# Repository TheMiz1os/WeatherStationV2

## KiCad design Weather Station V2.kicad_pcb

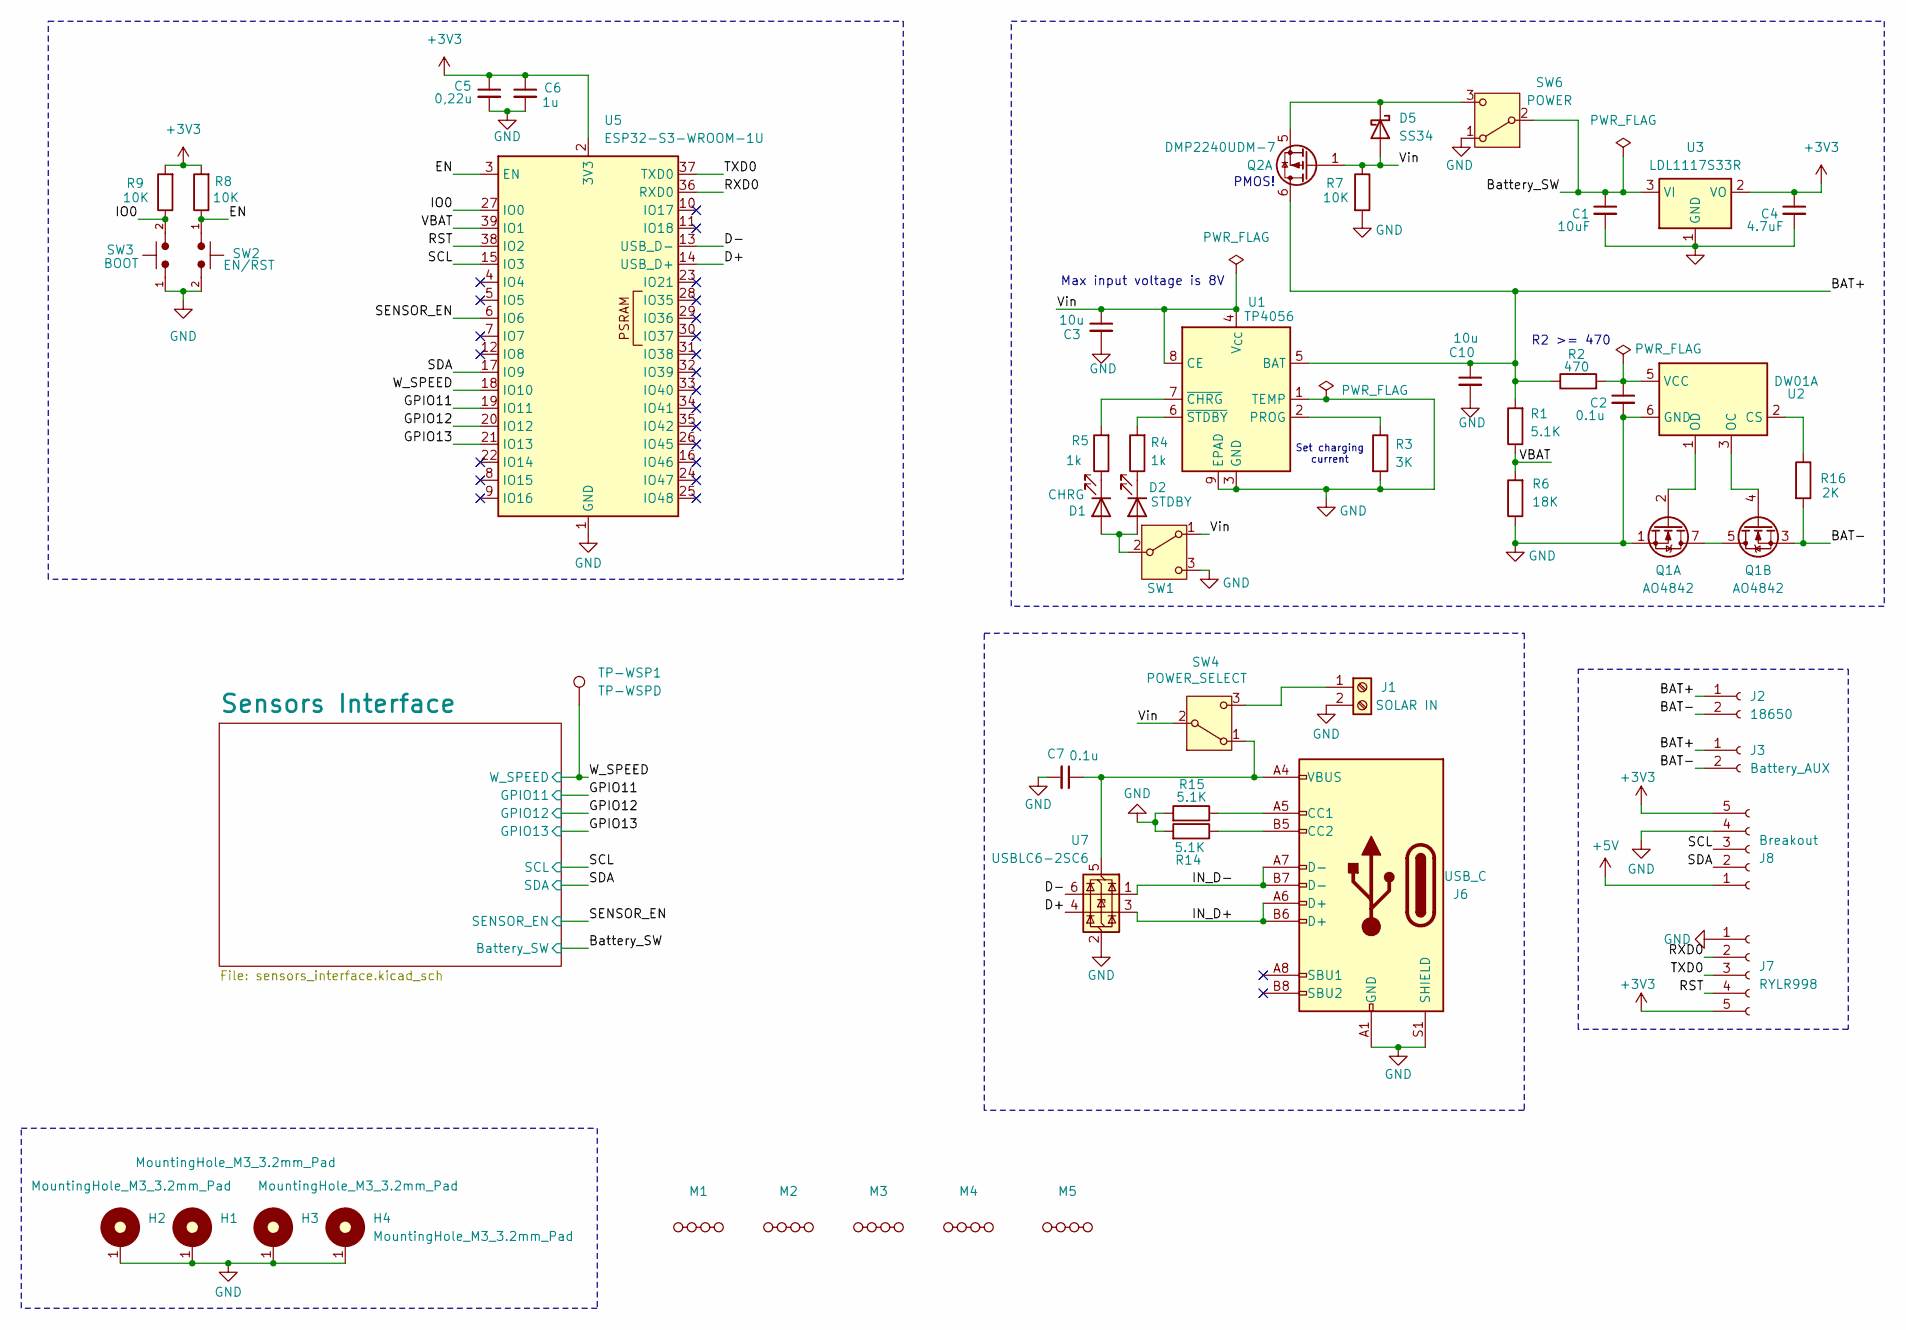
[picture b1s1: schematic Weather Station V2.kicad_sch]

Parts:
C1: 10uF; C_1206_3216Metric
C2, C7: 0.1u; C_1206_3216Metric
C3, C10: 10u; C_1206_3216Metric
C4: 4.7uF; C_1206_3216Metric
C5: 0,22u; C_1206_3216Metric
C6: 1u; C_1206_3216Metric
D1: CHRG; LED_1206_3216Metric
D2: STDBY; LED_1206_3216Metric
D5: SS34; D_SMA
H1, H2, H3, H4: MountingHole_M3_3.2mm_Pad; MountingHole_3.2mm_Pad
J1: SOLAR IN; TerminalBlock_MaiXu_MX126-5.0-02P_1x02_P5.00mm
J2: 18650; BatteryHolder_MPD_BH-18650-PC
J3: Battery_AUX; JST_EH_B2B-EH-A_1x02_P2.50mm_Vertical
J6: USB_C; USB_C_Receptacle_GCT_USB4105-xx-A_16P_TopMnt_Horizontal
J7: RYLR998; PinSocket_1x05_P2.54mm_Vertical
J8: Breakout; PinSocket_1x05_P2.54mm_Vertical
M1, M2, M3, M4, M5: MouseBites, Cosmetic, JLCPCB, 1.6mm
Q1: AO4842; SOIC-8_3.9x4.9mm_P1.27mm
Q2: DMP2240UDM-7; SOT-23-6_Handsoldering
R1, R14, R15: 5.1K; R_1206_3216Metric
R2: 470; R_1206_3216Metric
R3: 3K; R_1206_3216Metric
R4, R5: 1k; R_1206_3216Metric
R6: 18K; R_1206_3216Metric
R7, R8, R9: 10K; R_1206_3216Metric
R16: 2K; R_1206_3216Metric
SW1: LED_ENABLE; Slide_Switch_SPDT_P3mm_10x5x10mm
SW2: EN/RST; SW_PUSH_6mm
SW3: BOOT; SW_PUSH_6mm
SW4: POWER_SELECT; Slide_Switch_SPDT_P3mm_10x5x10mm
SW6: POWER; Slide_Switch_SPDT_P3mm_10x5x10mm
TP-WSP1: TP-WSPD; TestPoint_THTPad_D2.0mm_Drill1.0mm
U1: TP4056; SOIC-8-1EP_3.9x4.9mm_P1.27mm_EP2.41x3.3mm_ThermalVias
U2: DW01A; SOT-23-6_Handsoldering
U3: LDL1117S33R; SOT-223-3_TabPin2
U5: ESP32-S3-WROOM-1U
U7: USBLC6-2SC6; SOT-23-6

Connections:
+3V3: C4.1, C5.1, C6.1, J7.5, J8.5, R8.2, R9.2, U3.2 (VO), U5.2 (3V3); also elsewhere on the board
+5V: J8.1; also elsewhere on the board
/BAT+: C10.1, J2.1, J3.1, Q2.6 (D), R1.2, R2.1, U1.5 (BAT)
/BAT-: J2.2, J3.2, Q1.3 (S2), R16.2
/Battery_SW: C1.1, SW6.2 (B), U3.3 (VI); also elsewhere on the board
/D+: U5.14 (USB_D+), U7.4 (I/O2)
/D-: U5.13 (USB_D-), U7.6 (I/O1)
/EN: R8.1, SW2.1, U5.3 (EN)
/GPIO11: U5.19 (IO11); also elsewhere on the board
/GPIO12: U5.20 (IO12); also elsewhere on the board
/GPIO13: U5.21 (IO13); also elsewhere on the board
/IN_D+: J6.A6 (D+), J6.B6 (D+), U7.3 (I/O2)
/IN_D-: J6.A7 (D-), J6.B7 (D-), U7.1 (I/O1)
/IO0: R9.1, SW3.2, U5.27 (IO0)
/RST: J7.4, U5.38 (IO2)
/RXD0: J7.2, U5.36 (RXD0)
/SCL: J8.3, U5.15 (IO3); also elsewhere on the board
/SDA: J8.2, U5.17 (IO9); also elsewhere on the board
/SENSOR_EN: U5.6 (IO6); also elsewhere on the board
/TXD0: J7.3, U5.37 (TXD0)
/VBAT: R1.1, R6.2, U5.39 (IO1)
/Vin: C3.1, D5.2 (A), Q2.1 (G), R7.1, SW1.1 (A), SW4.2 (B), U1.4 (V_{CC}), U1.8 (CE)
/W_SPEED: TP-WSP1.1, U5.18 (IO10); also elsewhere on the board
GND: C1.2, C2.2, C3.2, C4.2, C5.2, C6.2, C7.2, C10.2, H1.1, H2.1, H3.1, H4.1, J1.2, J6.A1 (GND), J6.A12 (GND), J6.B1 (GND), J6.B12 (GND), J6.S1 (SHIELD), J7.1, J8.4, Q1.1 (S1), R3.2, R6.1, R7.2, R14.2, R15.2, SW1.3 (C), SW2.2, SW3.1, SW6.1 (A), U1.1 (TEMP), U1.3 (GND), U1.9 (EPAD), U2.6 (GND), U3.1 (GND), U5.1 (GND), U5.40 (GND), U5.41 (GND), U7.2 (GND); also elsewhere on the board
unnamed: D1.2 (A), D2.2 (A), SW1.2 (B)
unnamed: D1.1 (K), R5.1
unnamed: D2.1 (K), R4.1
unnamed: D5.1 (K), Q2.5 (S), SW6.3 (C)
unnamed: J1.1, SW4.3 (C)
unnamed: J6.A5 (CC1), R15.1
unnamed: J6.B5 (CC2), R14.1
unnamed: Q1.5 (D2), Q1.6 (D2), Q1.7 (D1), Q1.8 (D1)
unnamed: Q1.2 (G1), U2.1 (OD)
unnamed: Q1.4 (G2), U2.3 (OC)
unnamed: C7.1, J6.A4 (VBUS), J6.A9 (VBUS), J6.B4 (VBUS), J6.B9 (VBUS), SW4.1 (A), U7.5 (VBUS)
unnamed: R3.1, U1.2 (PROG)
unnamed: R5.2, U1.7 (~CHRG)
unnamed: R4.2, U1.6 (~STDBY)
unnamed: R16.1, U2.2 (CS)
unnamed: C2.1, R2.2, U2.5 (VCC)

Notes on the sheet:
R2 >= 470
PMOS!
Set charging current
Max input voltage is 8V

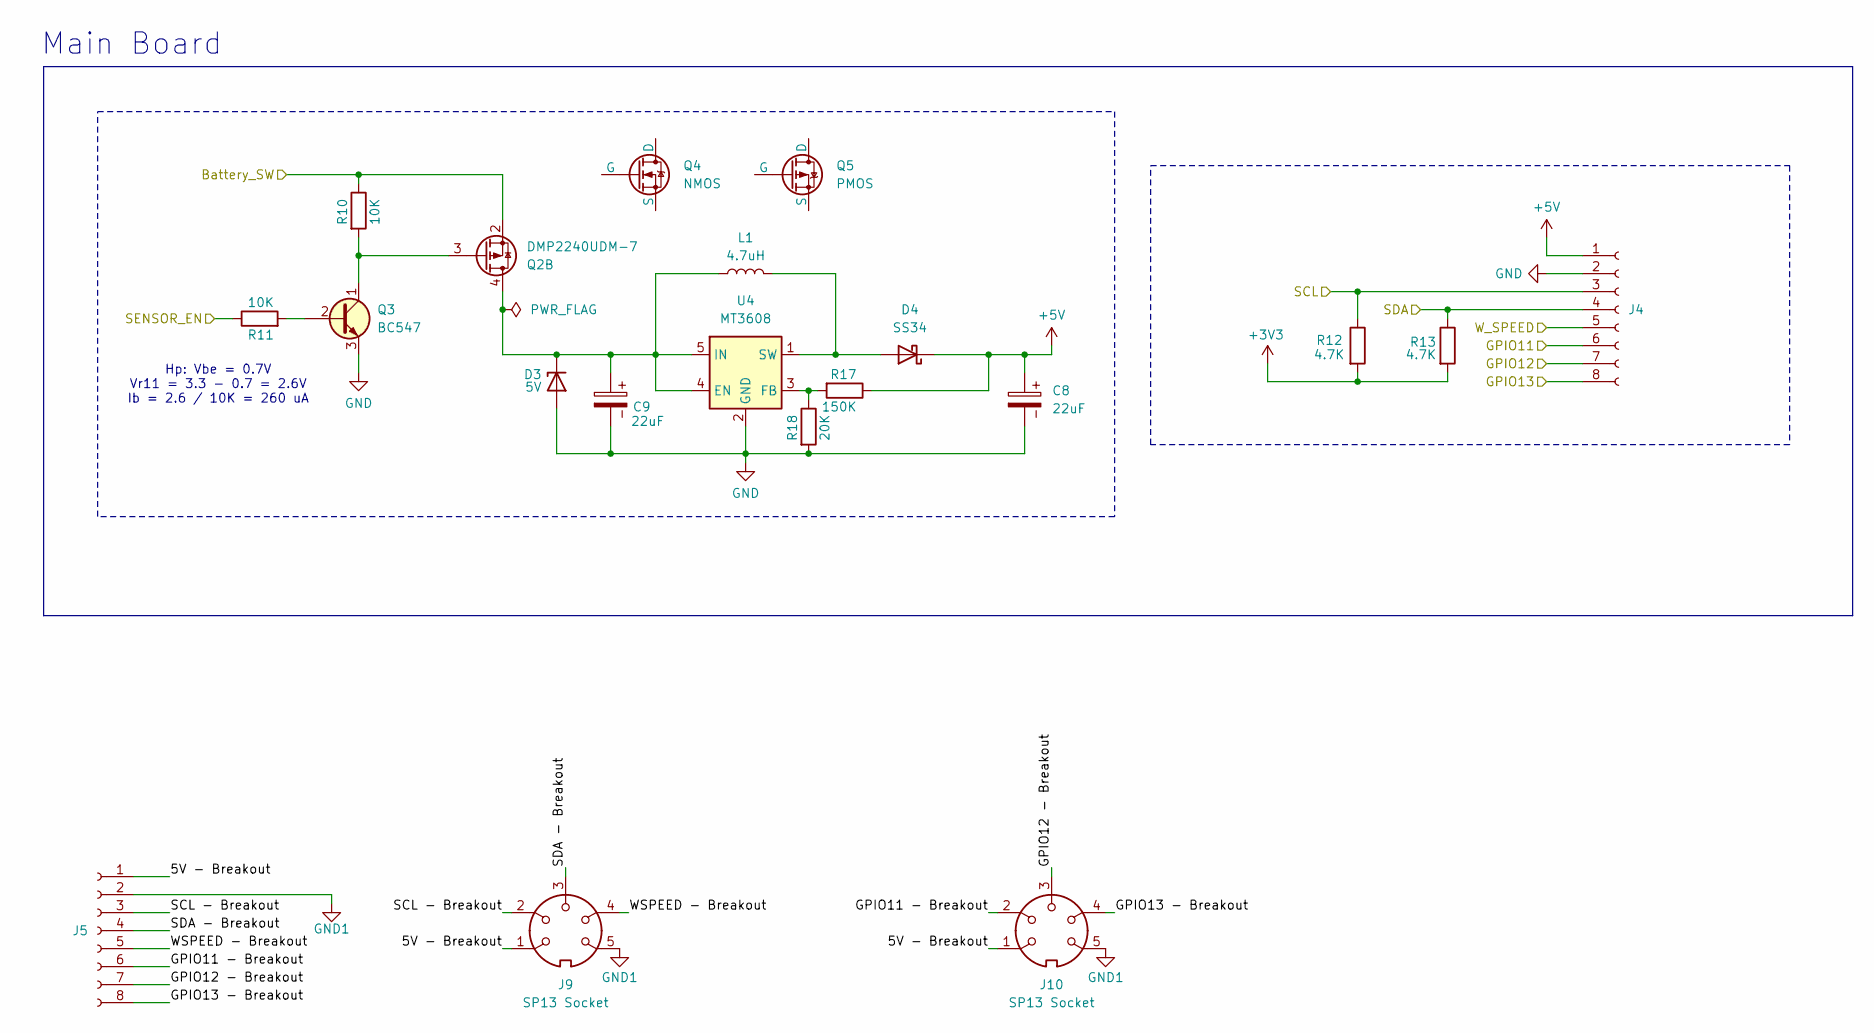
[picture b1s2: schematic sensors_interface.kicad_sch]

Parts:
C8, C9: 22uF; CP_Radial_D4.0mm_P1.50mm
D3: 5V; D_DO-41_SOD81_P10.16mm_Horizontal
D4: SS34; D_SMA
J4, J5: Conn_01x08_Socket; Hirose_DF13-08P-1.25DSA_1x08_P1.25mm_Vertical
J9, J10: SP13 Socket; SP13_5pin_holes
L1: 4.7uH; L_APV_APH0420
Q2: DMP2240UDM-7; SOT-23-6_Handsoldering
Q3: BC547; TO-92_Inline_Wide_CBE
Q4: NMOS
Q5: PMOS
R10, R11: 10K; R_1206_3216Metric
R12, R13: 4.7K; R_1206_3216Metric
R17: 150K; R_1206_3216Metric
R18: 20K; R_1206_3216Metric
U4: MT3608; SOT-23-6

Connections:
+3V3: R12.2, R13.2; also elsewhere on the board
+5V: C8.1, D4.1 (K), J4.1, R17.1; also elsewhere on the board
/Battery_SW: Q2.2 (S), R10.1; also elsewhere on the board
/GPIO11: J4.6; also elsewhere on the board
/GPIO12: J4.7; also elsewhere on the board
/GPIO13: J4.8; also elsewhere on the board
/SCL: J4.3, R12.1; also elsewhere on the board
/SDA: J4.4, R13.1; also elsewhere on the board
/SENSOR_EN: R11.1; also elsewhere on the board
/Sensors Interface/5V - Breakout: J5.1, J9.1, J10.1
/Sensors Interface/GPIO11 - Breakout: J5.6, J10.2
/Sensors Interface/GPIO12 - Breakout: J5.7, J10.3
/Sensors Interface/GPIO13 - Breakout: J5.8, J10.4
/Sensors Interface/SCL - Breakout: J5.3, J9.2
/Sensors Interface/SDA - Breakout: J5.4, J9.3
/Sensors Interface/WSPEED - Breakout: J5.5, J9.4
/W_SPEED: J4.5; also elsewhere on the board
GND: C8.2, C9.2, D3.2 (A), J4.2, Q3.3 (E), R18.2, U4.2 (GND); also elsewhere on the board
GND1: J5.2, J9.5, J10.5
unnamed: C9.1, D3.1 (K), L1.1, Q2.4 (D), U4.4 (EN), U4.5 (IN)
unnamed: D4.2 (A), L1.2, U4.1 (SW)
unnamed: Q2.3 (G), Q3.1 (C), R10.2
unnamed: Q3.2 (B), R11.2
unnamed: R17.2, R18.1, U4.3 (FB)

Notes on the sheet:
Main Board
Hp: Vbe = 0.7V Vr11 = 3.3 - 0.7 = 2.6V Ib = 2.6 / 10K = 260 uA

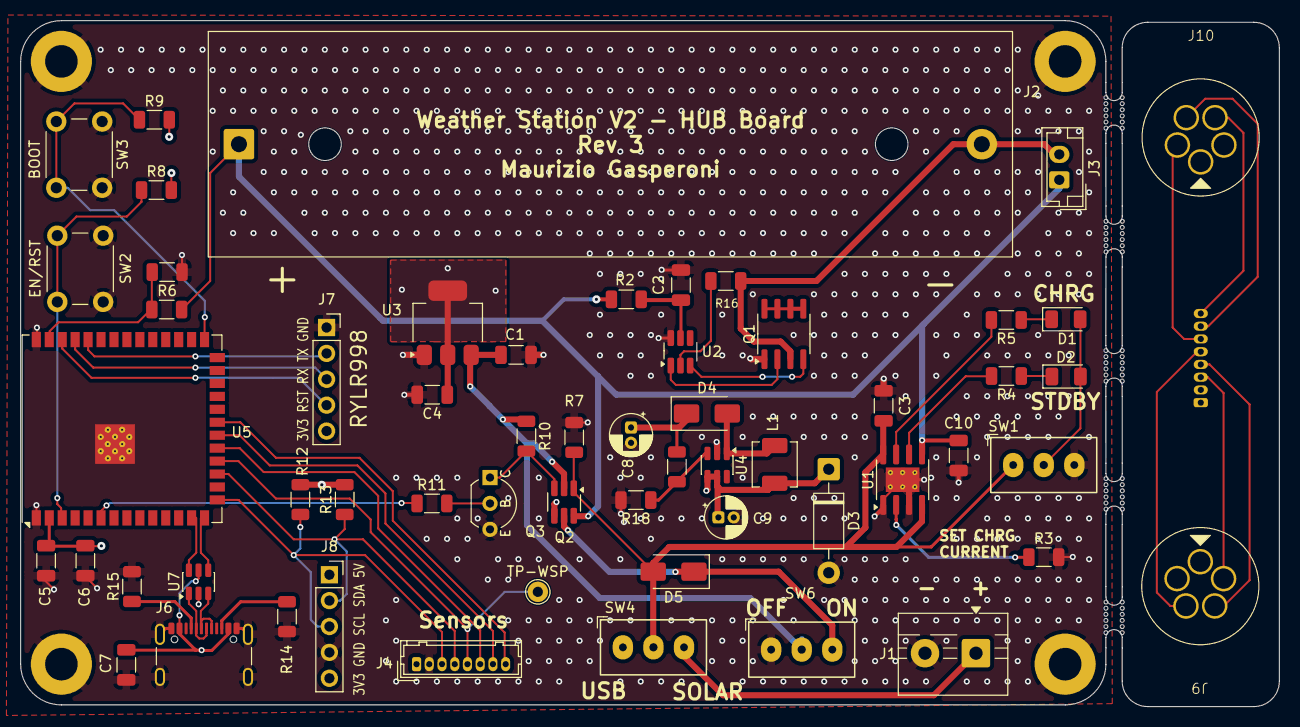
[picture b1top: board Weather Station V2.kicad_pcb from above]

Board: 4 copper layers, 123.5 x 67.3 mm, 68 parts (1 on the bottom side), 53 nets.

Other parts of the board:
TP-WSP: TP-WSPD; TestPoint_THTPad_D2.0mm_Drill1.0mm

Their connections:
/W_SPEED: TP-WSP.1 (1_1); also elsewhere on the board

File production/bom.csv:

Designator,Footprint,Quantity,Value,LCSC Part #
C1,1206,1,10uF,
"C2, C3, C7",1206,3,0.1u,
C4,1206,1,4.7uF,
C5,1206,1,"0,22u",
C6,1206,1,1u,
"C8, C9",CP_Radial_D4.0mm_P1.50mm,2,22uF,
D1,1206,1,CHRG,
D2,1206,1,STDBY,
D3,D_DO-41_SOD81_P10.16mm_Horizontal,1,5V,
"D4, D5",D_SMA,2,SS34,
"H1, H2, H3, H4",MountingHole_3.2mm_Pad,4,MountingHole_M3_3.2mm_Pad,
J1,TerminalBlock_MaiXu_MX126-5.0-02P_1x02_P5.00mm,1,SOLAR IN,
J2,BatteryHolder_MPD_BH-18650-PC,1,18650,
J3,JST_EH_B2B-EH-A_1x02_P2.50mm_Vertical,1,Battery_AUX,
J4,Hirose_DF13-08P-1.25DSA_1x08_P1.25mm_Vertical,1,Conn_01x08_Socket,
J6,USB_C_Receptacle_GCT_USB4105-xx-A_16P_TopMnt_Horizontal,1,USB_C,
J7,PinSocket_1x05_P2.54mm_Vertical,1,RYLR998,
J8,PinSocket_1x05_P2.54mm_Vertical,1,Breakout,
L1,L_APV_APH0420,1,4.7uH,
Q1,SOIC-8_3.9x4.9mm_P1.27mm,1,AO4842,
Q2,SOT-23-6_Handsoldering,1,DMP2240UDM-7,
Q3,TO-92_Inline_Wide_CBE,1,BC547,
"R1, R14, R15",1206,3,5.1K,
"R10, R11, R7, R8, R9",1206,5,10K,
"R12, R13",1206,2,4.7K,
R16,1206,1,5K,
R17,1206,1,150K,
R18,1206,1,20K,
R2,1206,1,100,
R3,1206,1,3K,
"R4, R5",1206,2,330,
R6,1206,1,18K,
SW1,Slide_Switch_SPDT_P3mm_10x5x10mm,1,LED_ENABLE,
SW2,SW_PUSH_6mm,1,EN/RST,
SW3,SW_PUSH_6mm,1,BOOT,
SW4,Slide_Switch_SPDT_P3mm_10x5x10mm,1,POWER_SELECT,
SW6,Slide_Switch_SPDT_P3mm_10x5x10mm,1,POWER,
U1,SOIC-8-1EP_3.9x4.9mm_P1.27mm_EP2.41x3.3mm_ThermalVias,1,TP4056,
U2,SOT-23-6_Handsoldering,1,DW01A,
U3,SOT-223-3_TabPin2,1,LDL1117S33R,
U4,SOT-23-6,1,MT3608,
U5,ESP32-S3-WROOM-1U,1,ESP32-S3-WROOM-1U,
U7,SOT-23-6,1,USBLC6-2SC6,

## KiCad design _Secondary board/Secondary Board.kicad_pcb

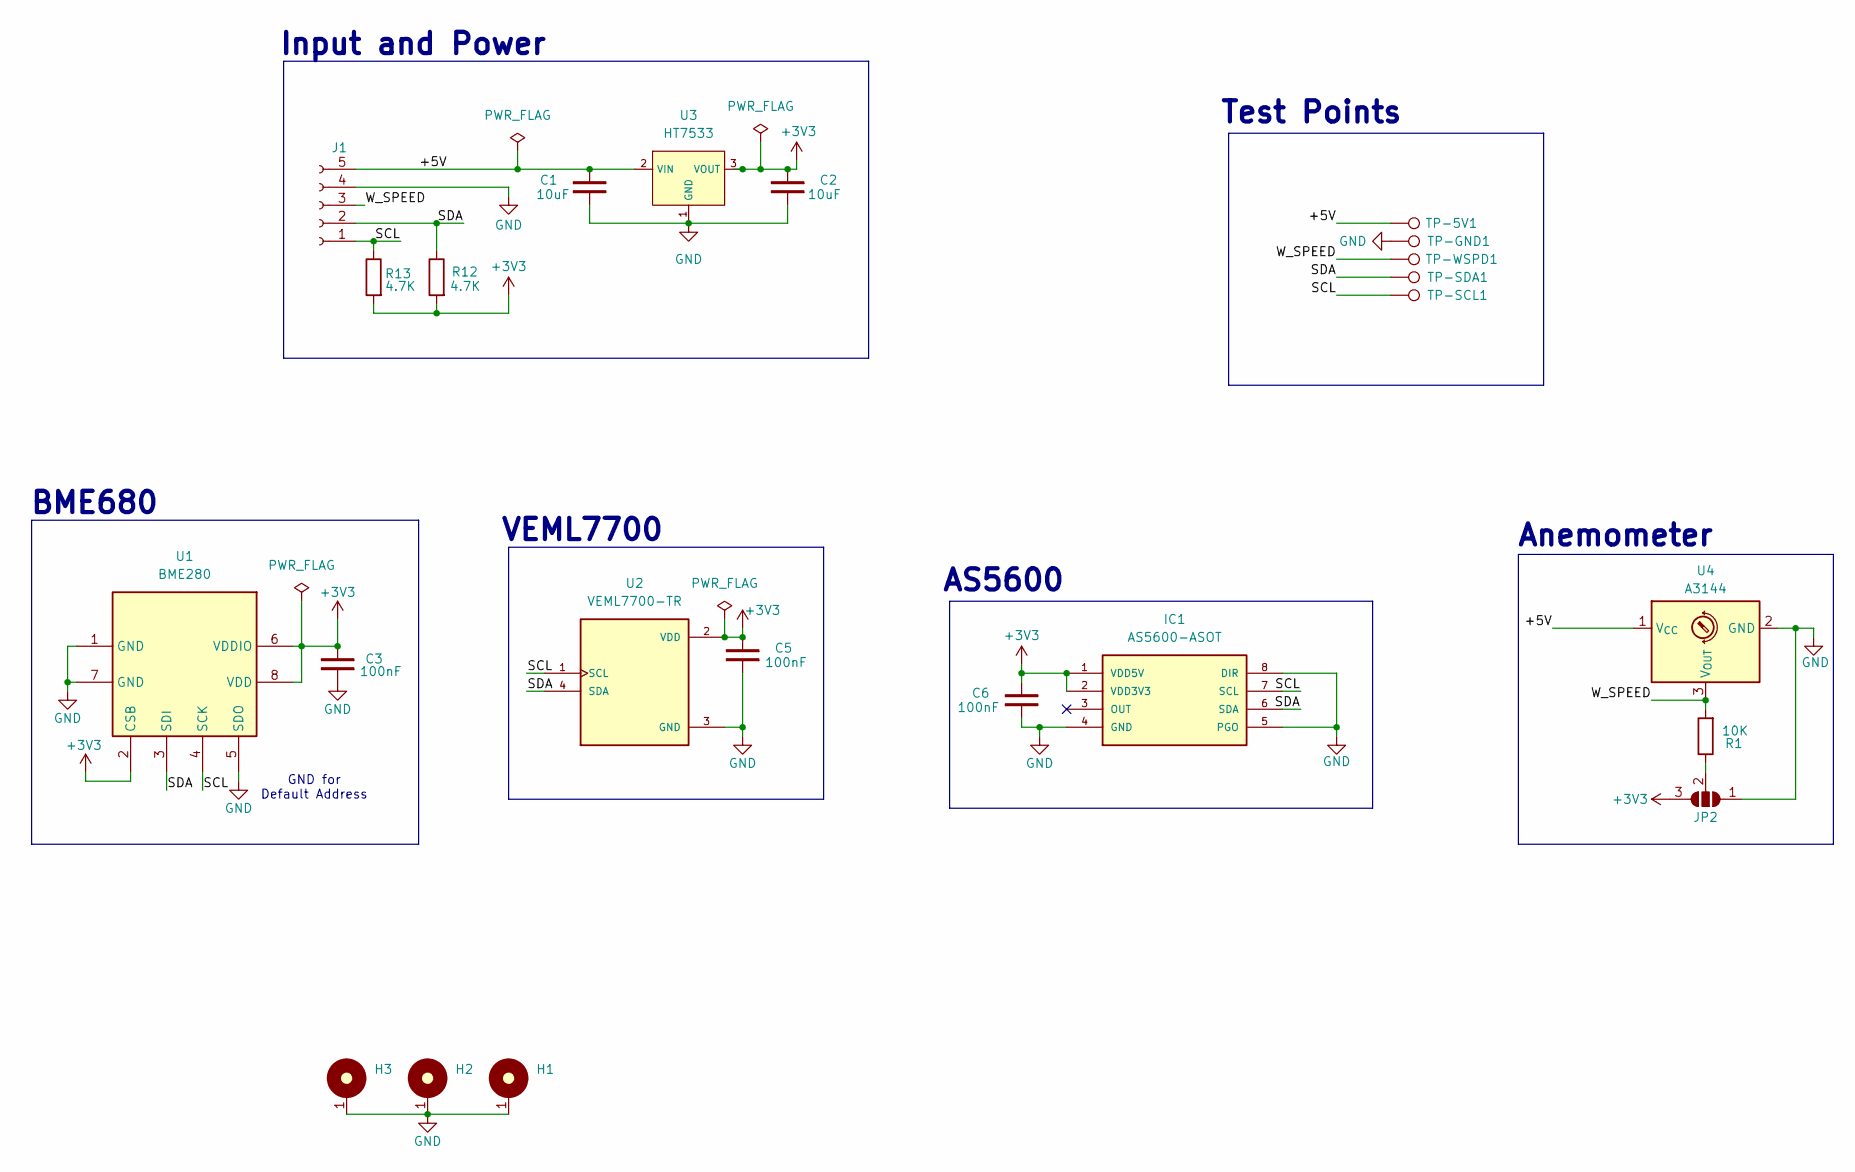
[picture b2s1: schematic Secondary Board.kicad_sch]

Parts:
C1, C2: 10uF; C_1206_3216Metric_Pad1.33x1.80mm_HandSolder
C3, C5, C6: 100nF; C_1206_3216Metric_Pad1.33x1.80mm_HandSolder
H1, H2, H3: MountingHole_M3_3.2mm_Pad; MountingHole_3.2mm_M3_ISO7380_Pad
IC1: AS5600-ASOT; SOIC127P600X175-8N; MOUSER_PART_NUMBER 985-AS5600-ASOT
J1: Conn_01x05_Socket; Hirose_DF13-05P-1.25DSA_1x05_P1.25mm_Vertical
JP2: SolderJumper_3_Open; SolderJumper-3_P1.3mm_Open_RoundedPad1.0x1.5mm
R1: 10K; R_1206_3216Metric
R12, R13: 4.7K; R_1206_3216Metric
TP-5V1: TestPoint; TestPoint_THTPad_D1.5mm_Drill0.7mm
TP-GND1: TestPoint; TestPoint_THTPad_D1.5mm_Drill0.7mm
TP-SCL1: TestPoint; TestPoint_THTPad_D1.5mm_Drill0.7mm
TP-SDA1: TestPoint; TestPoint_THTPad_D1.5mm_Drill0.7mm
TP-WSPD1: TestPoint; TestPoint_THTPad_D1.5mm_Drill0.7mm
U1: BME280; Bosch_LGA-8_2.5x2.5mm_P0.65mm_ClockwisePinNumbering
U2: VEML7700-TR; XDCR_VEML7700-TR; PARTREV 1.6; DigiKey_Part_Number VEML7700CT-ND
U3: HT7533; SOT-89-3_L4.5-W2.5-P1.50-LS4.2-BR; Output Voltage 3.3V; Dropout Voltage 55mV@(1mA); Part HT7533-1; LCSC C14289
U4: A3144; TO-92S

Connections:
+3V3: C2.2, C3.2, C5.2, C6.2, IC1.1 (VDD5V), IC1.2 (VDD3V3), JP2.3 (B), R12.2, R13.2, U1.2 (CSB), U1.6 (VDDIO), U1.8 (VDD), U2.2 (VDD), U3.3 (VOUT)
/+5V: C1.2, J1.5, TP-5V1.1 (1_1), U3.2 (VIN), U4.1 (V_{CC})
/SCL: IC1.7 (SCL), J1.1, R13.1, TP-SCL1.1 (1_1), U1.4 (SCK), U2.1 (SCL)
/SDA: IC1.6 (SDA), J1.2, R12.1, TP-SDA1.1 (1_1), U1.3 (SDI), U2.4 (SDA)
/W_SPEED: J1.3, R1.2, TP-WSPD1.1 (1_1), U4.3 (V_{OUT})
GND: C1.1, C2.1, C3.1, C5.1, C6.1, H1.1, H2.1, H3.1, IC1.4 (GND), IC1.5 (PGO), IC1.8 (DIR), J1.4, JP2.1 (A), TP-GND1.1 (1_1), U1.1 (GND), U1.5 (SDO), U1.7 (GND), U2.3 (GND), U3.1 (GND), U4.2 (GND)
unnamed: JP2.2 (C), R1.1

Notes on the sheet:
Anemometer
AS5600
VEML7700
Input and Power
GND for Default Address
BME680
Test Points

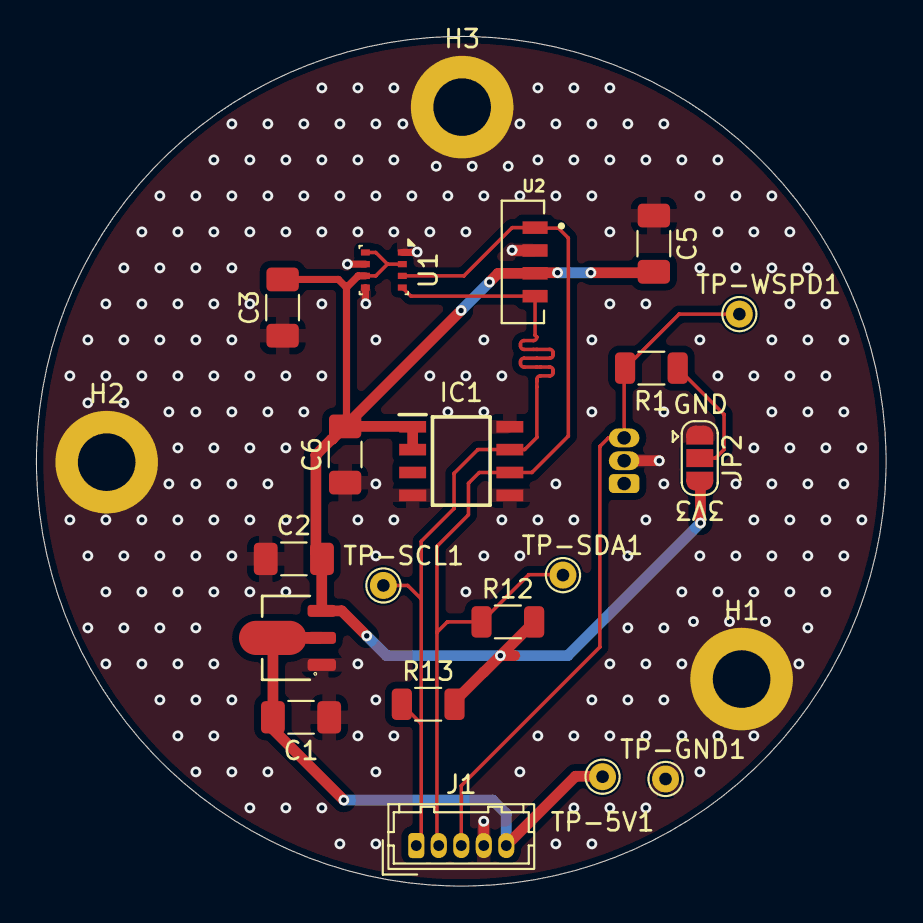
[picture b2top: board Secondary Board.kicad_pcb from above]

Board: 2 copper layers, 47.2 x 47.2 mm, 23 parts (1 on the bottom side), 7 nets.

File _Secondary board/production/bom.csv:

Designator,Footprint,Quantity,Value,LCSC Part #
"5V, GND, SCL, SDA, WSPD",TestPoint_THTPad_D1.5mm_Drill0.7mm,5,TestPoint,
"C1, C2",1206,2,10uF,
"C3, C5, C6",1206,3,100nF,
"H1, H2, H3",MountingHole_3.2mm_M3_ISO7380_Pad,3,MountingHole_M3_3.2mm_Pad,
IC1,SOIC127P600X175-8N,1,AS5600-ASOT,
J1,Hirose_DF13-05P-1.25DSA_1x05_P1.25mm_Vertical,1,Conn_01x05_Socket,
R1,1206,1,10K,
"R12, R13",1206,2,4.7K,
U1,Bosch_LGA-8_2.5x2.5mm_P0.65mm_ClockwisePinNumbering,1,BME280,
U2,XDCR_VEML7700-TR,1,VEML7700-TR,
U3,SOT-89-3_L4.5-W2.5-P1.50-LS4.2-BR,1,HT7533,C14289
U4,TO-92S,1,A3144,

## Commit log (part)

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2026-01-24 Initial Commit Full configuration with RJ45 Connector
2026-01-24 Updated .gitingnore and .gitattitrubes files
2026-01-24 Updated gitattributes to show right language
2026-01-24 Replaced RJ45 with 1x8 P1.25mm JST connector Fix: line ends normalization for kicad files
2026-01-24 Started the breakout board schematic
2026-02-06 Secondary Board now has the hall sensor interated Fixed BME680 schematic mistakes Updated gitignore
2026-02-06 Properly saved the files
2026-02-07 Replaced BME680 with BME280 Added Testpoints
2026-02-12 Added breakoout board - no panelization done yet Manufacturing capabilities have not been checked
2026-02-12 Added esp32 connection to charging status lines (CHRG 48, STDBY 47) Panelization with breakout board. Potentially final. Proably sending it soon
2026-02-12 Updated Production Files
2026-02-16 Now sensor power gets switched before 5V boost-coverter Reduced 3.3v plane size
2026-04-09 Updated to KiCAD 10.0 Final Commit before JCLPCB Order
2026-06-26 - Changed CHRG and STDBY pins to 48 and 47 (CHRG was strapping) - Exposed 5V rail do Breakout connector. Now also it matches a bme280 pinout for testing - Renamed BatteryReg net to Battery_SW - Fixed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
2026-06-26 - Changed 3V3 LDO to LDL1117S33R - In a previous commit ON OFF power lables were switched
